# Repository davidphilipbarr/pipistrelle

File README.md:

# pipistrelle
Attempt at diodeless plover board.

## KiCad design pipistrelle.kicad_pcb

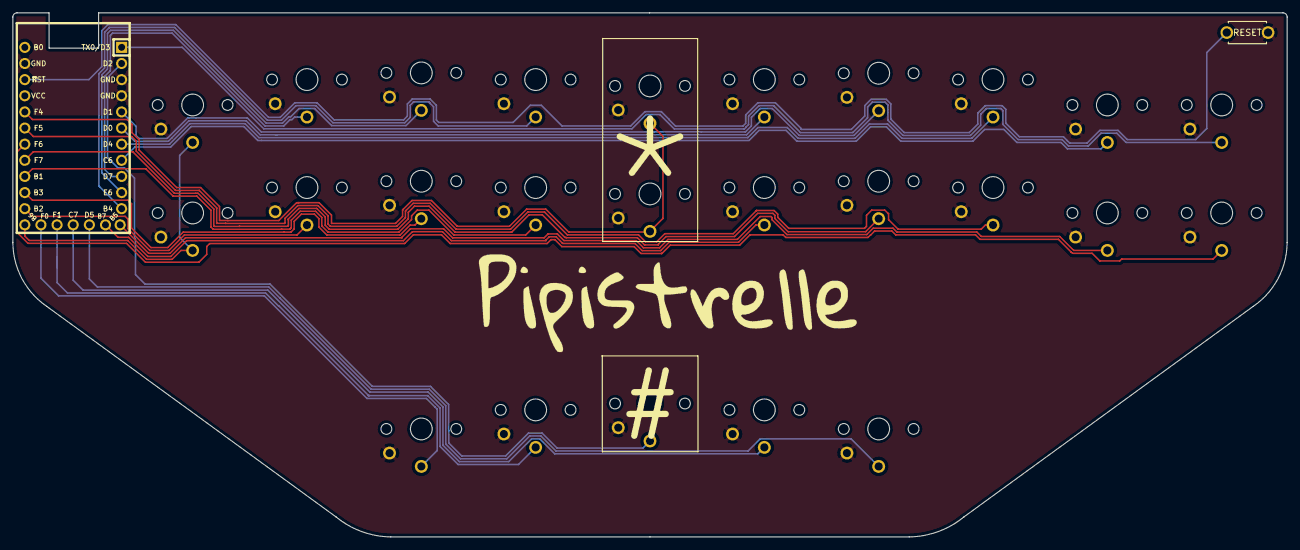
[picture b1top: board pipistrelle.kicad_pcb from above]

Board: 2 copper layers, 200.6 x 82.5 mm, 27 parts (1 on the bottom side), 25 nets.

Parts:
RSW1: SW_PUSH; ResetSW_1side
SW2, SW3, SW4, SW5, SW6, SW6#2, SW8, SW9, SW10, SW11, SW11#2, SW12, SW14, SW15, SW16, SW17, SW18, SW18#2, SW20, SW21, SW22, SW23, SW24, SW25, SW26: SW_Push; SW_PG1350_nonrev_DPB2
U1: ProMicro-kbd; Elite-C

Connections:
Switch1: SW2.1, U1.9
Switch2: SW3.1, U1.17
Switch3: SW4.1, U1.18
Switch4: SW5.1, U1.19
Switch5: SW6.1, SW6#2.1, U1.20
Switch6: SW8.1, U1.16
Switch7: SW9.1, U1.15
Switch8: SW10.1, U1.14
Switch9: SW11.1, SW11#2.1, U1.13
Switch10: SW12.1, U1.1
Switch11: SW14.1, U1.5
Switch12: SW15.1, U1.6
Switch13: SW16.1, U1.7
Switch14: SW17.1, U1.8
Switch15: SW18#2.1, U1.10
Switch16: SW20.1, U1.11
Switch17: SW21.1, U1.12
Switch18: SW18.1, U1.2
Switch19: SW22.1, U1.25
Switch20: SW23.1, U1.26
Switch21: SW24.1, U1.27
Switch22: SW25.1, U1.28
Switch23: SW26.1, U1.29
gnd: RSW1.1, SW2.2, SW3.2, SW4.2, SW5.2, SW6.2, SW6#2.2, SW8.2, SW9.2, SW10.2, SW11.2, SW11#2.2, SW12.2, SW14.2, SW15.2, SW16.2, SW17.2, SW18.2, SW18#2.2, SW20.2, SW21.2, SW22.2, SW23.2, SW24.2, SW25.2, SW26.2, U1.3, U1.4, U1.23
reset: RSW1.2, U1.22

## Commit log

2021-11-01 initial attempt, no one use!
2021-11-01 upload snap
2021-11-05 new attenpt
2021-11-05 small tidy
2021-11-26 add qmk
